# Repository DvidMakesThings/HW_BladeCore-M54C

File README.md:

# BladeCore‑M54C

BladeCore‑M54C is part of the **BladeCore** modular controller series.  
Each BladeCore variant is implemented as a standalone hardware repository, sharing a common architectural philosophy while targeting different microcontrollers and interfaces.

This repository documents the **BladeCore-M54C** hardware, which is based on the **RP2354B** microcontroller and integrates **CAN 2.0B connectivity**.

## BladeCore Series Overview

The BladeCore series consists of the following hardware variants:

| Module | Microcontroller | Primary Interface | Form Factor | Status |
|------|-----------------|-------------------|------------|-------------------|
| [BladeCore‑M40](#)  | RP2040  | —        | -          | Work in progress |
| [BladeCore‑M40E](#) | RP2040  | Ethernet | -          | Work in progress |
| [BladeCore‑M40C](#) | RP2040  | CAN      | -          | Work in progress |
| [BladeCore‑M54](#)  | RP2354B | —        | -          | Work in progress |
| [BladeCore-M54E](https://github.com/DvidMakesThings/HW_BladeCore-M54E) | RP2354B | Ethernet | 2980       | Available |
| [BladeCore-M54C](https://github.com/DvidMakesThings/HW_BladeCore-M54C) | RP2354B | CAN      | 2980       | Available |

### Naming Scheme Explanation

The BladeCore naming scheme encodes the **microcontroller family** and **primary communication interface** directly in the module name:

- **M40** designates an RP2040‑based module  
- **M54** designates an RP2354B‑based module  
- **E** suffix indicates integrated Ethernet support  
- **C** suffix indicates integrated CAN support  

Variants without a suffix represent the **base module** for that microcontroller family, without Ethernet or CAN integrated.

Each BladeCore variant is implemented as a **separate hardware design and repository**.

## Description

BladeCore-M54C is a compact controller module built around the **RP2354B** microcontroller, combined with a **MCP2515T-I/ML CAN controller** and the **TCAN1044AVDRBRQ1** CAN transceiver.  
The module is designed as a **2980-size M.2 M-Key card**, intended to be embedded into a carrier board or system that provides power through the M.2 edge connector.

The design integrates:

*   RP2354B microcontroller
*   External QSPI flash memory
*   External I²C EEPROM
*   Onboard CAN controller and transceiver with 120 Ohm termination
*   Dual‑path USB connectivity with automatic source selection
*   Onboard power regulation and defined power‑up sequencing

This repository contains the schematics and documentation.

- [BladeCore‑M54 schematics (PDF)](src/PDF/BladeCore-M54C_Schematics.pdf).
- [BladeCore‑M54 KiCad folder](src/HardwareDesign/1.0.0/).

### Resources

- **KiCad Libraries:** [src/HardwareDesign/Libraries/KiCad](src/HardwareDesign/Libraries/KiCad)
    - BladeCore‑M54C footprint 
    - BladeCore‑M54C symbol
    - Plain M.2 connector footprint (MDT420E03001)
    - 3D STEP: BladeCore‑M54C + MDT420E03001 assembly
    - 3D STEP: M.2 connector
- **Eagle Libraries:** [src/HardwareDesign/Libraries/Eagle](src/HardwareDesign/Libraries/Eagle)
    - Status: Work in progress

## Hardware Overview

<table>
    <tr>
        <td align="center">
            <br><em>Top view</em>
        </td>
        <td align="center">
            <br><em>Bottom view</em>
        </td>
    </tr>
 </table>

### Form Factor

*   **M.2 2980**
*   **M‑Key**
*   Power and I/O routed through the M.2 edge connector

### Microcontroller

*   **RP2354B**
*   External **12 MHz crystal**
*   Internal 1.1 V core supply generated by the MCU
*   SWD debug interface available
*   GPIOs routed to the M.2 edge connector

### Memory

*   **Integrated Flash**
    *   RP2354B
    *   Capacity: **2 MB**
*   **External QSPI Flash**
    *   W25Q128JVPIQ
    *   Capacity: **16 MB**
*   **External I²C EEPROM**
    *   AT24C256
    *   Capacity: **256 kbit**

***

### CAN

*   **MCP2515T-I/ML CAN controller**
*   **TCAN1044AVDRBRQ1** CAN transceiver
*   Interface to MCU via **SPI**
*   Onboard 120 Ohm termination
*   Dedicated reset and interrupt signals
*   ESD protection

### USB

BladeCore‑M54C supports **two physical USB connection paths**:

1.  **USB routed through the M.2 edge connector** (external host or carrier board USB), and
2.  **Onboard USB‑C connector**.

A **FSUSB42 USB 2.0 high‑speed multiplexer** is used to select which USB path is connected to the RP2354B.

**USB path selection behavior:**

*   By default, the USB data lines are routed to the **M.2 edge connector**.
*   When the **onboard USB‑C connector is plugged in**, the FSUSB42 automatically **redirects the USB data path** from the edge connector to the onboard USB‑C connector.
*   Removing the onboard USB connection restores the default routing to the M.2 edge connector.

This allows the module to be normally operated via a carrier board USB connection, while still enabling direct access through the onboard USB‑C connector when needed, without manual configuration.

***

### Power

*   Input supply: **VBUS / 5 V / 3.3 V** (5V and 3.3V is selectable by onboard solder jumper)
*   **TPS74801** low‑dropout regulator generating 3.3 V in case of 5V power is selected
*   Power‑good signaling with visal feedback (LED)
*   USB VBUS sensing routed to ADC
*   Optional USB‑powered operation depending on component population (as noted in schematics)

### M.2 Connector Pinout

#### Left Side (Odd Pins)

| Pin | Name | F0 | F1 | F2 | F3 | F4 | F5 | F6 | F7 | F8 | F9 |
|----:|------|----|----|----|----|----|----|----|----|----|----| 
| 1 | GND | | | | | | | | | | |
| 3 | GPIO24 | SPI0 TX | UART1 RTS | I2C1 SCL | PWM3 B | SIO | PIO0 | PIO1 | PIO2 | | CLOCK GPOUT1 |
| 5 | GPIO23 | SPI0 TX | UART1 RTS | I2C1 SCL | PWM3 B | SIO | PIO0 | PIO1 | PIO2 | | CLOCK GPOUT1 |
| 7 | GPIO22 | SPI0 SCK | UART1 CTS | I2C1 SDA | PWM3 A | SIO | PIO0 | PIO1 | PIO2 | | CLOCK GPIN1 |
| 9 | GPIO21 | SPI0 CSn | UART1 RX | **I2C0 SCL | PWM2 B | SIO | PIO0 | PIO1 | PIO2 | | CLOCK GPOUT0 |
| 11 | GND | | | | | | | | | | |
| 13 | GPIO20 | SPI0 RX | UART1 TX | **I2C0 SDA | PWM2 A | SIO | PIO0 | PIO1 | PIO2 | | CLOCK GPIN0 |
| 15 | GPIO19 | SPI0 TX | UART0 RTS | I2C1 SCL | PWM1 B | SIO | PIO0 | PIO1 | PIO2 | | QMI CS1n |
| 17 | GPIO18 | SPI0 SCK | UART0 CTS | I2C1 SDA | PWM1 A | SIO | PIO0 | PIO1 | PIO2 | | |
| 19 | GPIO17 | SPI0 CSn | UART0 RX | **I2C0 SCL | PWM0 B | SIO | PIO0 | PIO1 | PIO2 | | |
| 21 | GPIO16 | SPI0 RX | UART0 TX | **I2C0 SDA | PWM0 A | SIO | PIO0 | PIO1 | PIO2 | | |
| 23 | GND | | | | | | | | | | |
| 25 | GPIO15 | *SPI1 TX | UART0 RTS | I2C1 SCL | PWM7 B | SIO | PIO0 | PIO1 | PIO2 | | CLOCK GPOUT1 |
| 27 | GPIO14 | *SPI1 SCK | UART0 CTS | I2C1 SDA | PWM7 A | SIO | PIO0 | PIO1 | PIO2 | | CLOCK GPIN1 |
| 29 | GPIO13 | *SPI1 CSn | UART0 RX | **I2C0 SCL | PWM6 B | SIO | PIO0 | PIO1 | PIO2 | | CLOCK GPOUT0 |
| 31 | GPIO12 | *SPI1 RX | UART0 TX | **I2C0 SDA | PWM6 A | SIO | PIO0 | PIO1 | PIO2 | | CLOCK GPIN0 |
| 33 | GPIO11 | *SPI1 TX | UART1 RTS | I2C1 SCL | PWM5 B | SIO | PIO0 | PIO1 | PIO2 | | |
| 35 | GPIO10 | *SPI1 SCK | UART1 CTS | I2C1 SDA | PWM5 A | SIO | PIO0 | PIO1 | PIO2 | | |
| 37 | GPIO9 | *SPI1 CSn | UART1 RX | **I2C0 SCL | PWM4 B | SIO | PIO0 | PIO1 | PIO2 | | |
| 39 | GPIO8 | *SPI1 RX | UART1 TX | **I2C0 SDA | PWM4 A | SIO | PIO0 | PIO1 | PIO2 | | QMI CS1n |
| 41 | GND | | | | | | | | | | |
| 43 | GPIO7 | SPI0 TX | UART1 RTS | I2C1 SCL | PWM3 B | SIO | PIO0 | PIO1 | PIO2 | | |
| 45 | GPIO6 | SPI0 SCK | UART1 CTS | I2C1 SDA | PWM3 A | SIO | PIO0 | PIO1 | PIO2 | | |
| 47 | GPIO5 | SPI0 CSn | UART1 RX | **I2C0 SCL | PWM2 B | SIO | PIO0 | PIO1 | PIO2 | | |
| 49 | GPIO4 | SPI0 RX | UART1 TX | **I2C0 SDA | PWM2 A | SIO | PIO0 | PIO1 | PIO2 | | |
| 51 | GPIO3 | SPI0 TX | UART0 RTS | I2C1 SCL | PWM1 B | SIO | PIO0 | PIO1 | PIO2 | | |
| 53 | GPIO2 | SPI0 SCK | UART0 CTS | I2C1 SDA | PWM1 A | SIO | PIO0 | PIO1 | PIO2 | | |
| 55 | GPIO1 | SPI0 CSn | UART0 RX | **I2C0 SCL | PWM0 B | SIO | PIO0 | PIO1 | PIO2 | | TRACECLK |
| 57 | GPIO0 | SPI0 RX | UART0 TX | **I2C0 SDA | PWM0 A | SIO | PIO0 | PIO1 | PIO2 | | QMI CS1n |
| 67 | GND | | | | | | | | | | |
| 69 | USB_D+ | | | | | | | | | | |
| 71 | USB_D- | | | | | | | | | | |
| 73 | GND | | | | | | | | | | |
| 75 | VBUS | | | | | | | | | | |

#### Right Side (Even Pins)

| Pin | Name | F0 | F1 | F2 | F3 | F4 | F5 | F6 | F7 | F8 | F9 |
|----:|------|----|----|----|----|----|----|----|----|----|----| 
| 2 | GND | | | | | | | | | | |
| 4 | GPIO27 | *SPI1 TX | UART1 RTS | I2C1 SCL | PWM5 B | SIO | PIO0 | PIO1 | PIO2 | | |
| 6 | GPIO26 | *SPI1 SCK | UART1 CTS | I2C1 SDA | PWM5 A | SIO | PIO0 | PIO1 | PIO2 | | |
| 8 | GPIO25 | *SPI1 CSn | UART1 RX | **I2C0 SCL | PWM4 B | SIO | PIO0 | PIO1 | PIO2 | | CLOCK GPOUT3 |
| 10 | 3V3_OUT | | | | | | | | | | |
| 12 | 3V3_OUT | | | | | | | | | | |
| 14 | +5V_IN | | | | | | | | | | |
| 16 | +5V_IN | | | | | | | | | | |
| 18 | GND | | | | | | | | | | |
| 20 | GND | | | | | | | | | | |
| 22 | GND | | | | | | | | | | |
| 24 | GND | | | | | | | | | | |
| 26 | GND | | | | | | | | | | |
| 28 | CAN_P | | | | | | | | | | |
| 30 | CAN_N | | | | | | | | | | |
| 32 | GND | | | | | | | | | | |
| 34 | GPIO37 |  | SPI0 CSn | UART1 RX | **I2C0 SCL | PWM10 B | SIO | PIO0 | PIO1 | PIO2 |  |
| 36 | GPIO38 |  | SPI0 SCK | UART1 CTS | I2C1 SDA | PWM11 A | SIO | PIO0 | PIO1 | PIO2 |  |
| 38 | GND | | | | | | | | | | |
| 40 | GPIO39 |  | SPI0 TX | UART1 RTS | I2C1 SCL | PWM11 B | SIO | PIO0 | PIO1 | PIO2 |  |
| 42 | GND | | | | | | | | | | |
| 44 | GND | | | | | | | | | | |
| 46 | ADC0/GPIO40 |  | *SPI1 RX | UART1 TX | **I2C0 SDA | PWM8 A | SIO | PIO0 | PIO1 | PIO2 |  |
| 48 | ADC1/GPIO41 |  | *SPI1 CSn | UART1 RX | **I2C0 SCL | PWM8 B | SIO | PIO0 | PIO1 | PIO2 |  |
| 50 | ADC2/GPIO42 |  | *SPI1 SCK | UART1 CTS | I2C1 SDA | PWM9 A | SIO | PIO0 | PIO1 | PIO2 |  |
| 52 | ADC3/GPIO43 |  | *SPI1 TX | UART1 RTS | I2C1 SCL | PWM9 B | SIO | PIO0 | PIO1 | PIO2 |  |
| 54 | ADC4/GPIO44 |  | *SPI1 RX | UART0 TX | **I2C0 SDA | PWM10 A | SIO | PIO0 | PIO1 | PIO2 |  |
| 56 | ADC5/GPIO45 |  | *SPI1 CSn | UART0 RX | **I2C0 SCL | PWM10 B | SIO | PIO0 | PIO1 | PIO2 |  |
| 58 | GND | | | | | | | | | | |
| 68 | GND | | | | | | | | | | |
| 70 | GND | | | | | | | | | | |
| 72 | VBUS | | | | | | | | | | |
| 74 | VBUS | | | | | | | | | | |
| SH1 | SHIELD | | | | | | | | | | |

*SPI1 is used for the onboard CAN controller (MCP2515T)

**I2C0 is used for the onboard EEPROM (AT24C256)

## Revision History

| Revision | Date       | Notes            |
| -------- | ---------- | ---------------- |
| 1.0.0    | 2026‑01‑31 | Initial creation |

## Notes

*   This documentation intentionally avoids assumptions about firmware features, supported protocols, or software behavior.
*   All statements are derived from the provided schematics and explicit design notes.
*   Component‑level limits and behavior should be verified against the respective datasheets.

## License
### Hardware Components
Hardware designs, schematics, and related documentation are licensed under the **Creative Commons Attribution-NonCommercial-ShareAlike 4.0 International License (CC BY-NC-SA 4.0)**. See the [Hardware License](LICENSE-CC-BY-NC-SA) file for details.

#### What CC BY-NC-SA 4.0 means:

- ✅ **You can** study, modify, and distribute the hardware designs
- ✅ **You can** create derivative works for personal, educational, or non-commercial use
- ✅ **You can** build this project for your own personal use

- ⚠️ **You must** give appropriate credit and indicate if changes were made
- ⚠️ **You must** share any modifications under the same license terms
- ⚠️ **You must** include the original license and copyright notices

- ❌ **You cannot** use the designs for commercial purposes without explicit permission
- ❌ **You cannot** manufacture and sell products based on these designs without a commercial license
- ❌ **You cannot** create closed-source derivatives for commercial purposes
- ❌ **You cannot** use the designer's trademarks without permission

### Commercial & Enterprise Use

Commercial use of this project is prohibited without obtaining a separate commercial license. If you are interested in:

- Manufacturing and selling products based on these designs
- Incorporating these designs into commercial products
- Any other commercial applications

Please contact me through any of the channels listed in the [Contact](#contact) section to discuss commercial licensing arrangements. Commercial licenses are available with reasonable terms to support ongoing development.

## Contact

For questions or feedback:
- **Email:** [info@dmt-hw.com](mailto:info@dmt-hw.com)
- **GitHub:** [DvidMakesThings](https://github.com/DvidMakesThings)

## Contributing

Contributions are welcome! As this is an early-stage project, please reach out before 
making substantial changes:

1. Fork the repository
2. Create a feature branch (`git checkout -b feature/concept`)
3. Commit your changes (`git commit -m 'Add concept'`)
4. Push to the branch (`git push origin feature/concept`)
5. Open a Pull Request with a detailed description

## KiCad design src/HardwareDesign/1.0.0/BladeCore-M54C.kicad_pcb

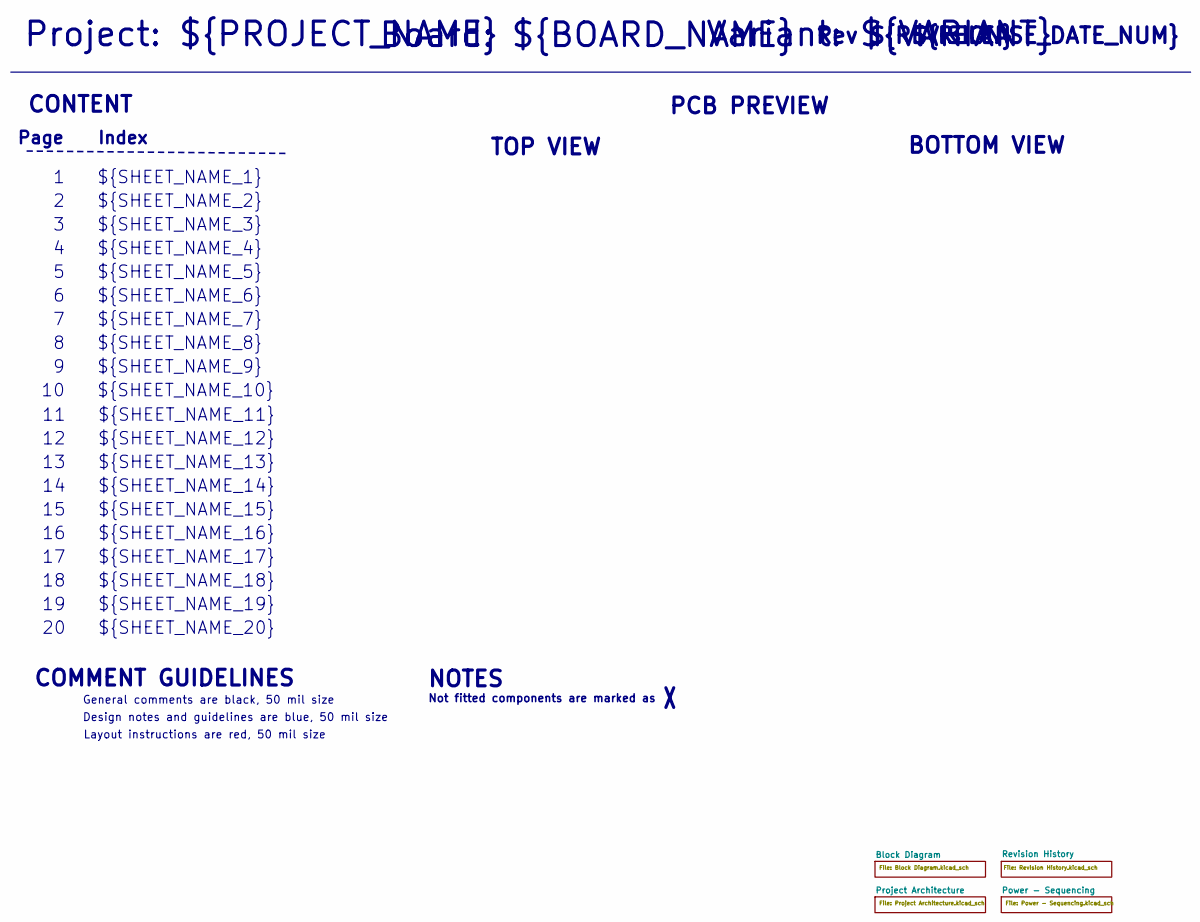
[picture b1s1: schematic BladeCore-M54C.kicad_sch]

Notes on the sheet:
${SHEET_NAME_12}
${SHEET_NAME_8}
${SHEET_NAME_2}
${SHEET_NAME_5}
${SHEET_NAME_20}
Page
PCB PREVIEW
${RELEASE_DATE_NUM}
CONTENT
${SHEET_NAME_11}
${SHEET_NAME_6}
Rev ${REVISION}
${SHEET_NAME_15}
BOTTOM VIEW
${SHEET_NAME_14}
${SHEET_NAME_17}
${SHEET_NAME_18}
${SHEET_NAME_7}
Not fitted components are marked as
Project: ${PROJECT_NAME}
NOTES
Design notes and guidelines are blue, 50 mil size
${SHEET_NAME_1}
${SHEET_NAME_9}
Board: ${BOARD_NAME}
General comments are black, 50 mil size
${SHEET_NAME_16}
${SHEET_NAME_3}
Variant: ${VARIANT}
${SHEET_NAME_19}
TOP VIEW
${SHEET_NAME_10}
Index
${SHEET_NAME_13}
${SHEET_NAME_4}
COMMENT GUIDELINES
Layout instructions are red, 50 mil size

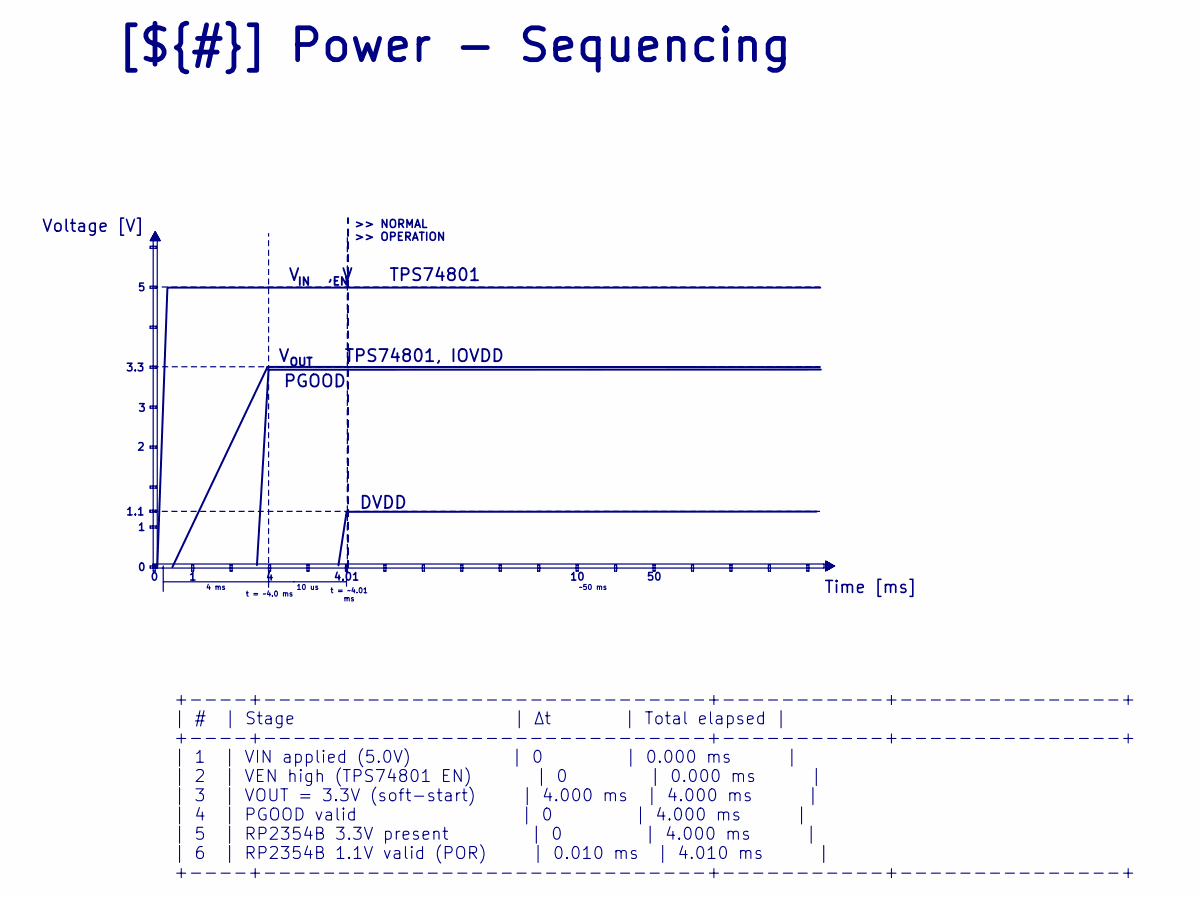
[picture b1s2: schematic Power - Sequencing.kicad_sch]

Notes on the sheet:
Voltage [V]
+----+------------------------------+-----------+---------------+ | # | Stage | Δt | Total elapsed | +----+------------------------------+-----------+---------------+ | 1 | VIN applied (5.0V) | 0 | 0.000 ms | | 2 | VEN high (TPS74801 EN) | 0 | 0.000 ms | | 3 | VOUT = 3.3V (soft-start) | 4.000 ms | 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
>> NORMAL >> OPERATION
Time [ms]
10 us
4.01
DVDD
t = ~4.01 ms
3.3
~50 ms
V , V TPS74801
t = ~4.0 ms
PGOOD
1.1
4 ms
OUT
V TPS74801, IOVDD
[${#}] ${TITLE}

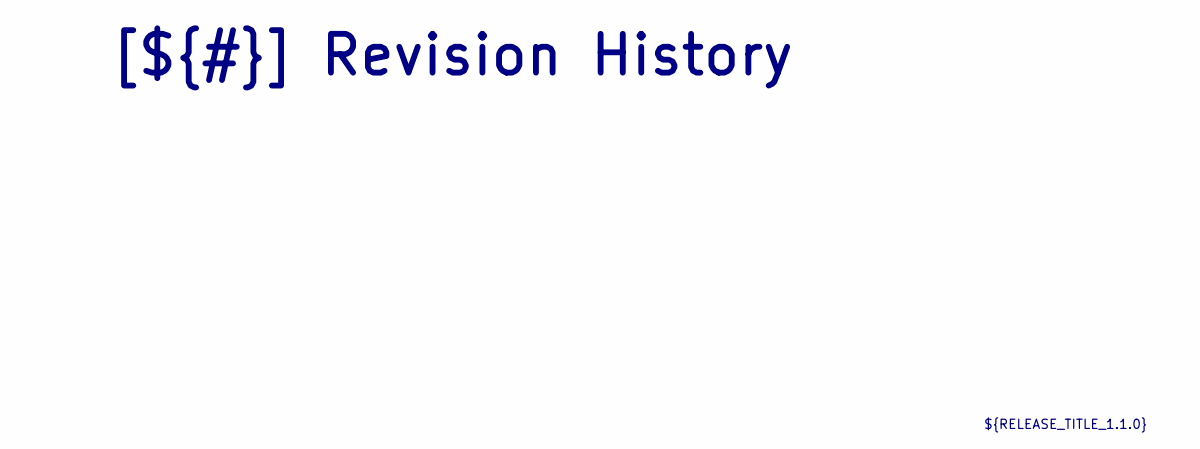
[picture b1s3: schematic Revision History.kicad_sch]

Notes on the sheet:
[${#}] ${TITLE}
${RELEASE_TITLE_1.1.0}

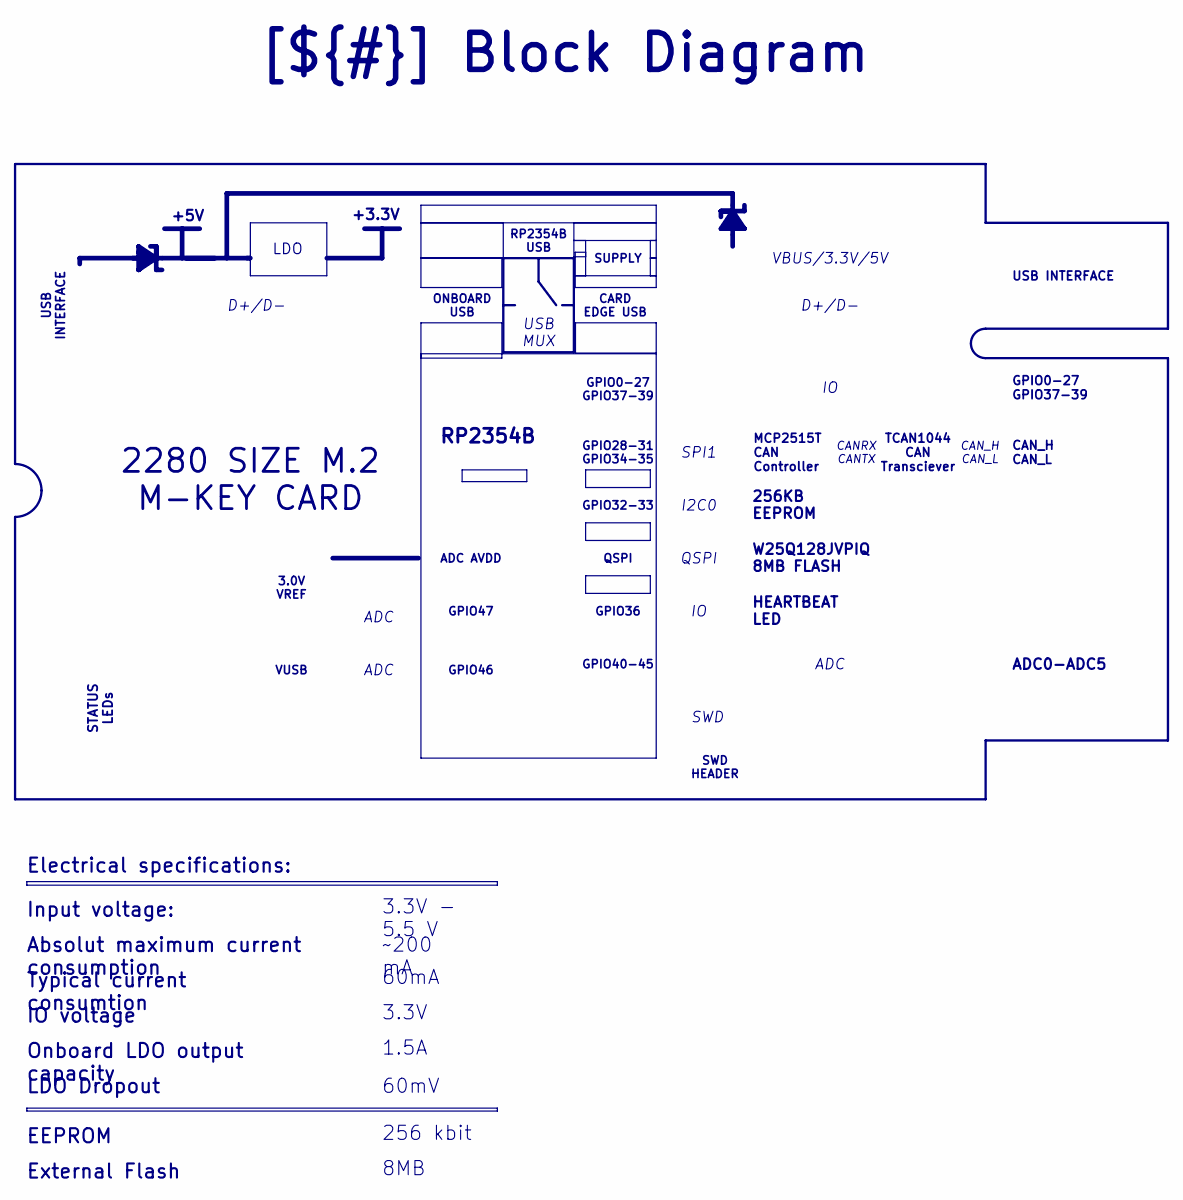
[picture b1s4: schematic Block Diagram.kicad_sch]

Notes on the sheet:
+3.3V
RP2354B
2280 SIZE M.2 M-KEY CARD
+5V
USB INTERFACE
LDO Dropout
IO voltage
256KB EEPROM
VBUS/3.3V/5V
1.5A
CARD EDGE USB
W25Q128JVPIQ 8MB FLASH
3.3V - 5.5 V
ADC0-ADC5
SWD HEADER
LDO
3.3V
GPIO0-27 GPIO37-39
CAN_H CAN_L
SPI1
MCP2515T CAN Controller
TCAN1044 CAN Transciever
GPIO40-45
ADC
QSPI
3.0V VREF
RP2354B USB
GPIO32-33
[${#}] ${TITLE}
~200 mA
Input voltage:
STATUS LEDs
EEPROM
GPIO46
256 kbit
Electrical specifications:
SWD
GPIO47
GPIO36
GPIO28-31 GPIO34-35

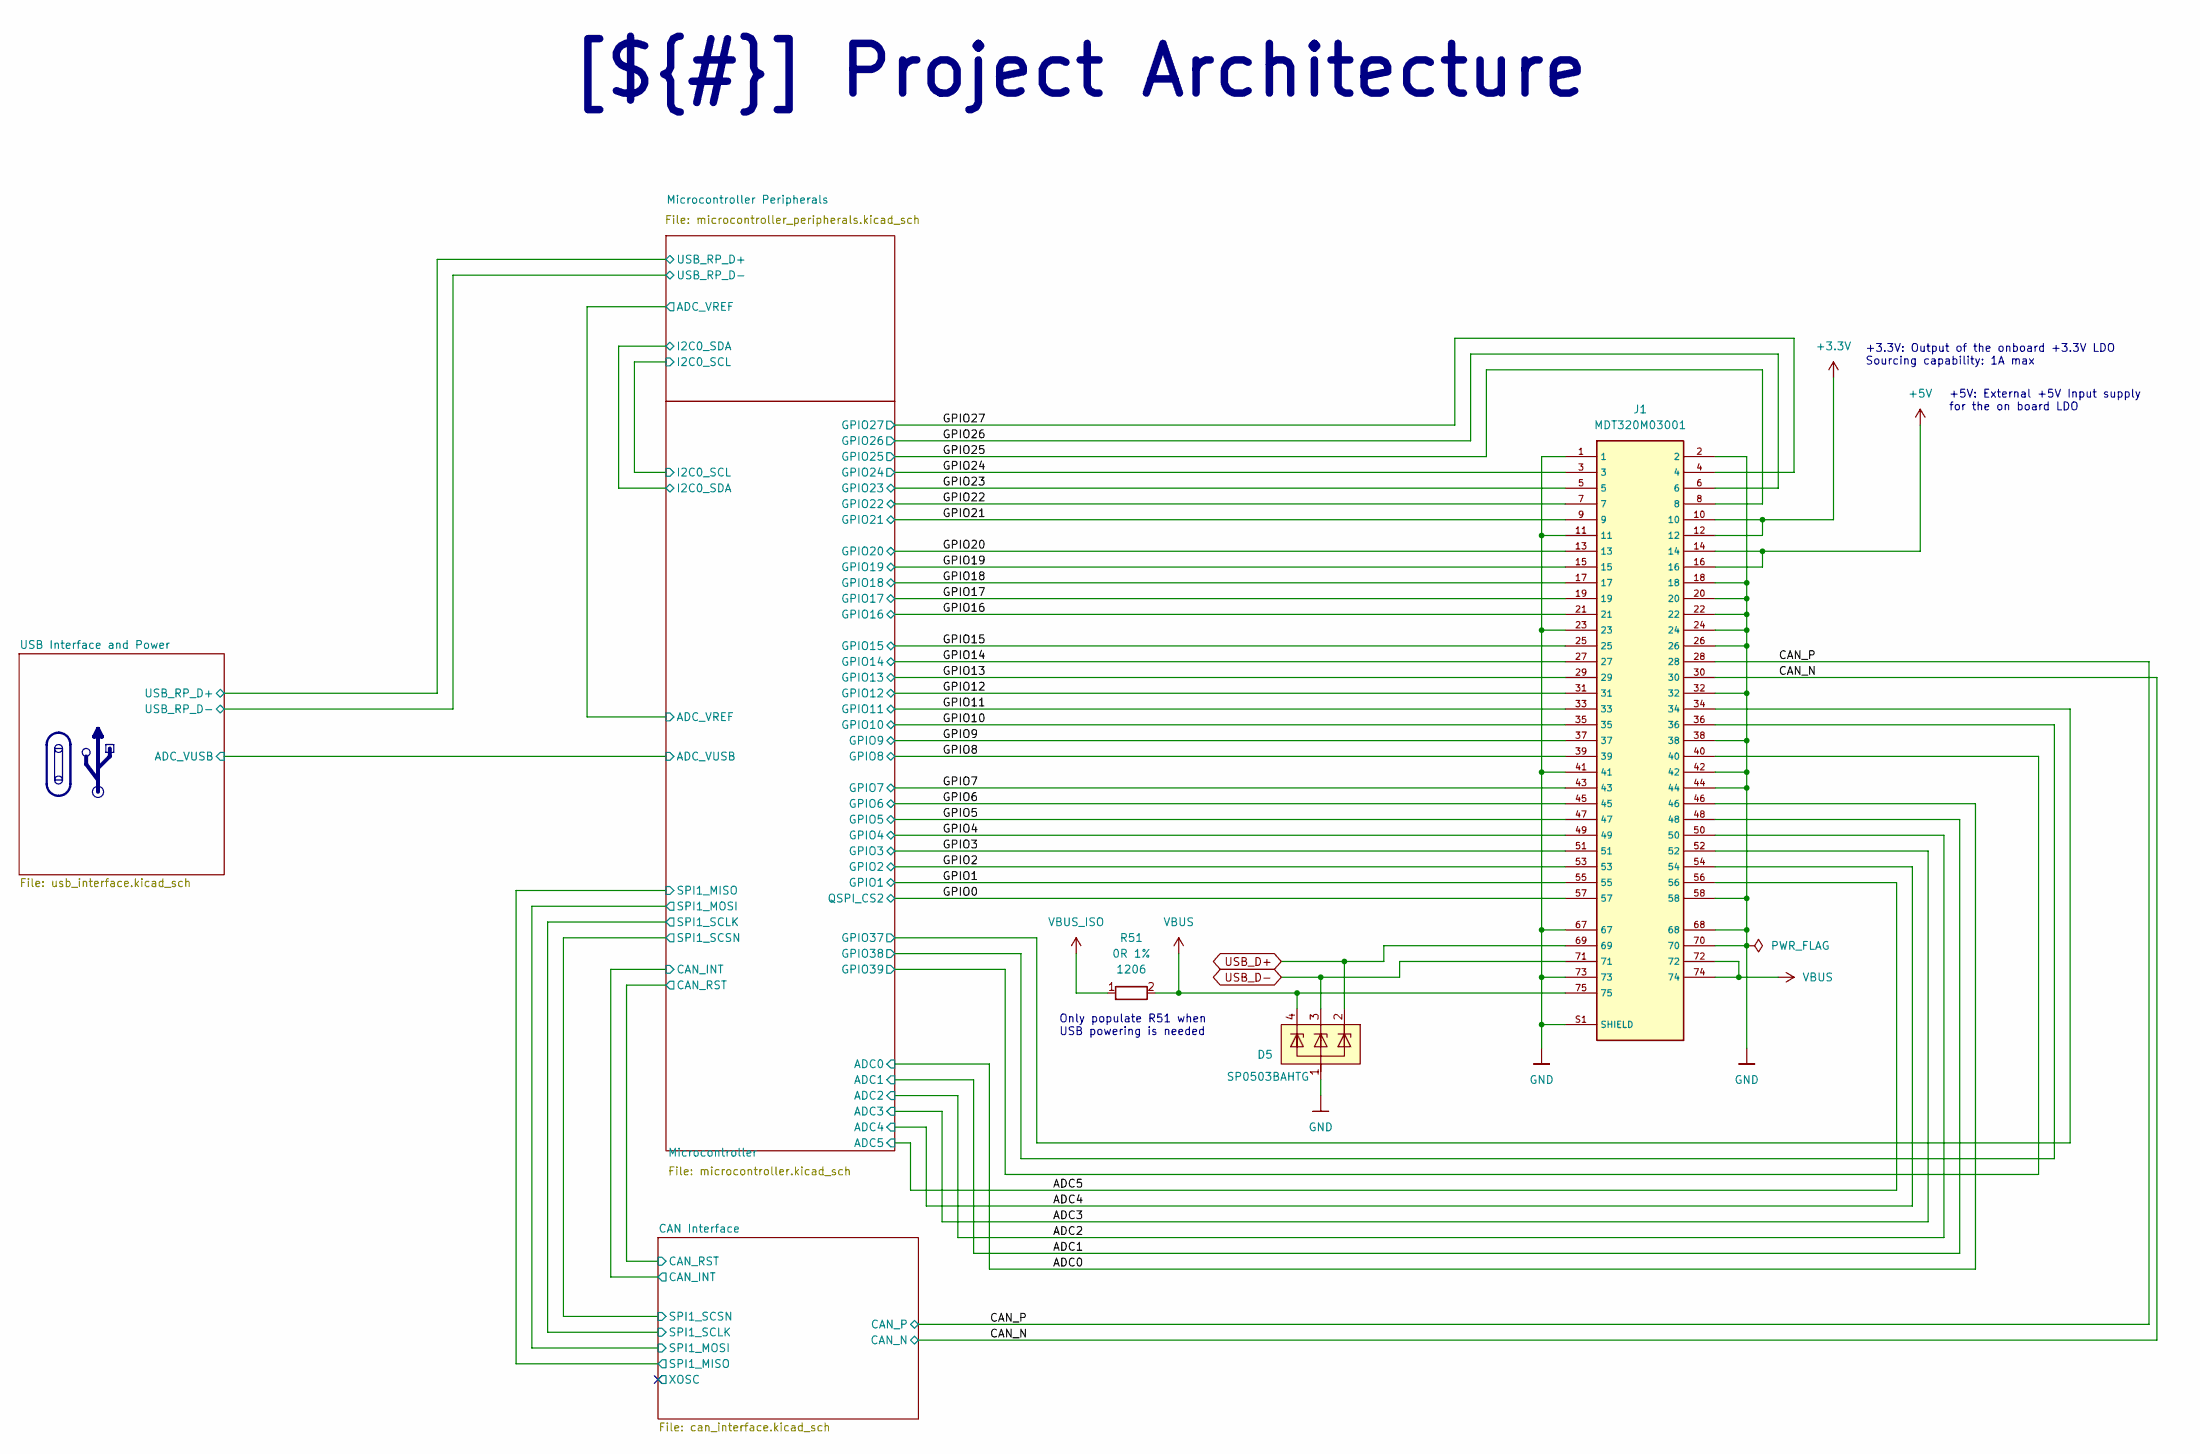
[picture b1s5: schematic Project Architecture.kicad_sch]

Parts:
D5: SP0503BAHTG; SOT143; MPN SP0503BAHTG; LCSC_PART C3040626
J1: MDT320M03001; M.2-M-KEY_Card_Plain
R51: 0R 1%; R_1206_3216Metric; LCSC_PART C205296

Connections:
+3.3V: J1.10, J1.12; also elsewhere on the board
+5V: J1.14, J1.16; also elsewhere on the board
/Project Architecture/ADC0: J1.46; also elsewhere on the board
/Project Architecture/ADC1: J1.48; also elsewhere on the board
/Project Architecture/ADC2: J1.50; also elsewhere on the board
/Project Architecture/ADC3: J1.52; also elsewhere on the board
/Project Architecture/ADC4: J1.54; also elsewhere on the board
/Project Architecture/ADC5: J1.56; also elsewhere on the board
/Project Architecture/CAN_N: J1.30; also elsewhere on the board
/Project Architecture/CAN_P: J1.28; also elsewhere on the board
/Project Architecture/GPIO0: J1.57; also elsewhere on the board
/Project Architecture/GPIO1: J1.55; also elsewhere on the board
/Project Architecture/GPIO2: J1.53; also elsewhere on the board
/Project Architecture/GPIO3: J1.51; also elsewhere on the board
/Project Architecture/GPIO4: J1.49; also elsewhere on the board
/Project Architecture/GPIO5: J1.47; also elsewhere on the board
/Project Architecture/GPIO6: J1.45; also elsewhere on the board
/Project Architecture/GPIO7: J1.43; also elsewhere on the board
/Project Architecture/GPIO8: J1.39; also elsewhere on the board
/Project Architecture/GPIO9: J1.37; also elsewhere on the board
/Project Architecture/GPIO10: J1.35; also elsewhere on the board
/Project Architecture/GPIO11: J1.33; also elsewhere on the board
/Project Architecture/GPIO12: J1.31; also elsewhere on the board
/Project Architecture/GPIO13: J1.29; also elsewhere on the board
/Project Architecture/GPIO14: J1.27; also elsewhere on the board
/Project Architecture/GPIO15: J1.25; also elsewhere on the board
/Project Architecture/GPIO16: J1.21; also elsewhere on the board
/Project Architecture/GPIO17: J1.19; also elsewhere on the board
/Project Architecture/GPIO18: J1.17; also elsewhere on the board
/Project Architecture/GPIO19: J1.15; also elsewhere on the board
/Project Architecture/GPIO20: J1.13; also elsewhere on the board
/Project Architecture/GPIO21: J1.9; also elsewhere on the board
/Project Architecture/GPIO22: J1.7; also elsewhere on the board
/Project Architecture/GPIO23: J1.5; also elsewhere on the board
/Project Architecture/GPIO24: J1.3; also elsewhere on the board
/Project Architecture/GPIO25: J1.8; also elsewhere on the board
/Project Architecture/GPIO26: J1.6; also elsewhere on the board
/Project Architecture/GPIO27: J1.4; also elsewhere on the board
/Project Architecture/Microcontroller/GPIO37: J1.34; also elsewhere on the board
/Project Architecture/Microcontroller/GPIO38: J1.36; also elsewhere on the board
/Project Architecture/Microcontroller/GPIO39: J1.40; also elsewhere on the board
GND: D5.1, J1.1, J1.2, J1.11, J1.18, J1.20, J1.22, J1.23, J1.24, J1.26, J1.32, J1.38, J1.41, J1.42, J1.44, J1.58, J1.67, J1.68, J1.70, J1.73, J1.S1 (SHIELD); also elsewhere on the board
USB_D+: D5.2, J1.69; also elsewhere on the board
USB_D-: D5.3, J1.71; also elsewhere on the board
VBUS: D5.4, J1.72, J1.74, J1.75, R51.2; also elsewhere on the board
VBUS_ISO: R51.1; also elsewhere on the board

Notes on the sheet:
Only populate R51 when USB powering is needed
+3.3V: Output of the onboard +3.3V LDO Sourcing capability: 1A max
+5V: External +5V Input supply for the on board LDO
[${#}] ${TITLE}

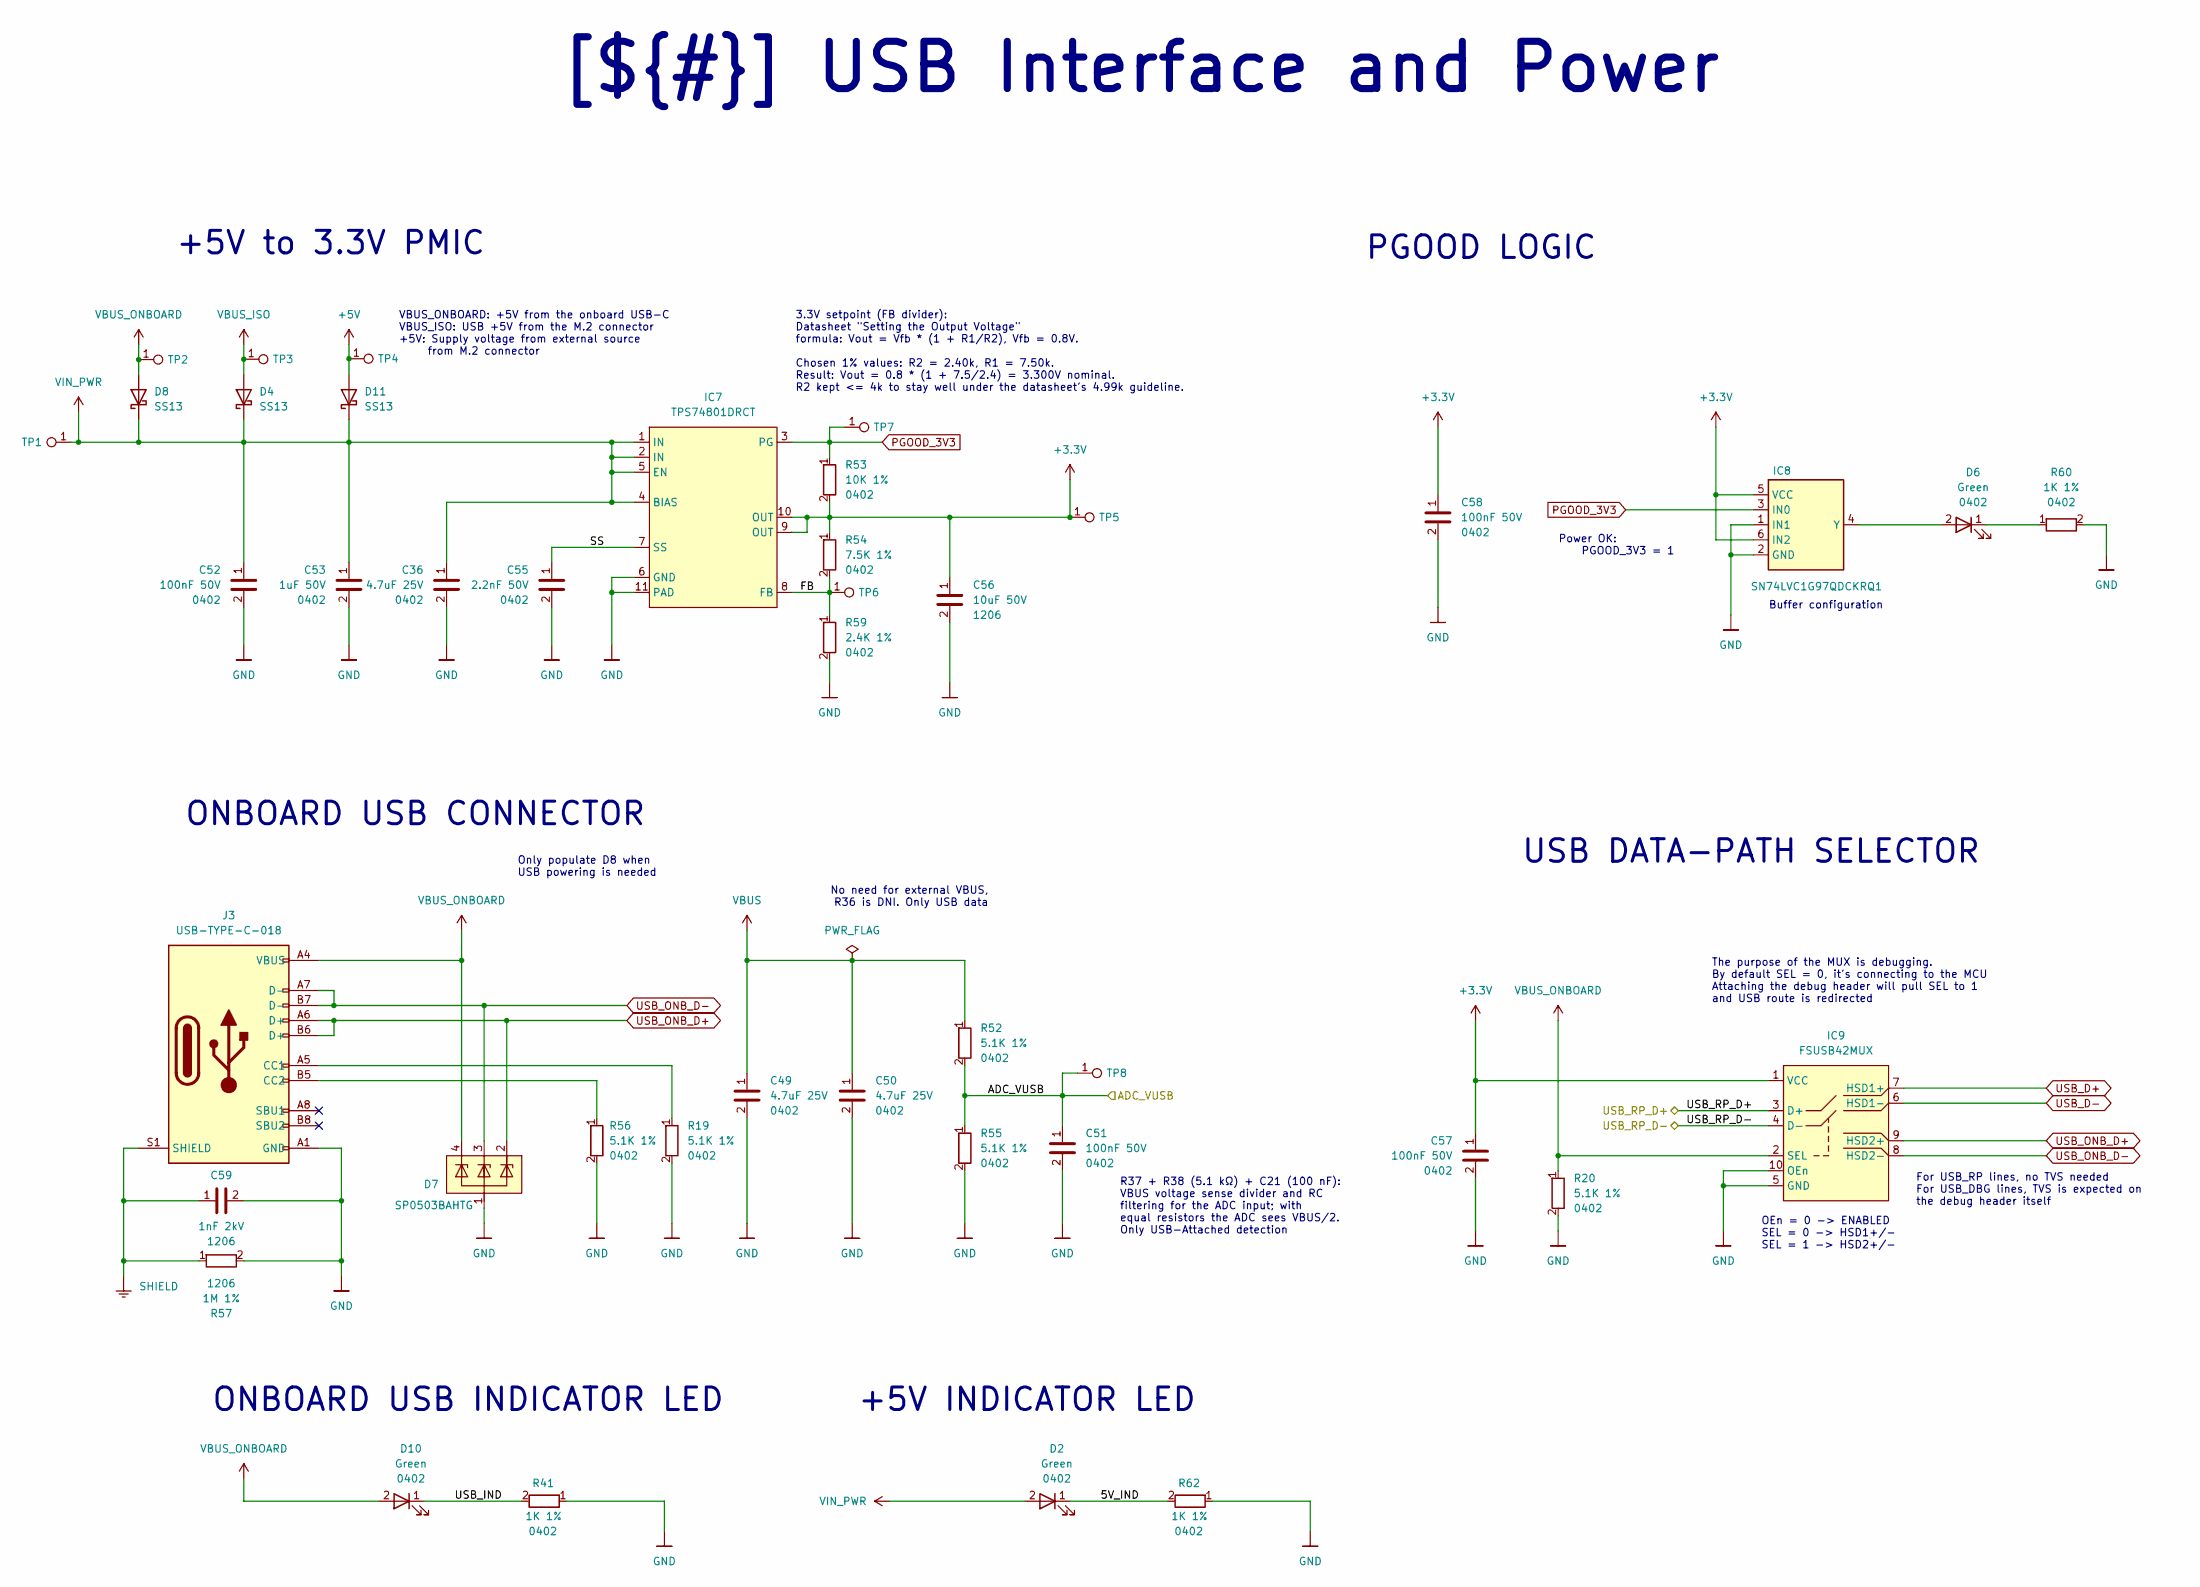
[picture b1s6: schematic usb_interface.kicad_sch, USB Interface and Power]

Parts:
C36, C49, C50: 4.7uF 25V; C_0402_1005Metric; LCSC_PART C22367824
C51, C52, C57, C58: 100nF 50V; C_0402_1005Metric; LCSC_PART C307331
C53: 1uF 50V; C_0402_1005Metric; LCSC_PART C1518208
C55: 2.2nF 50V; C_0402_1005Metric; MPN CC0402KRX7R9BB222; LCSC_PART C106861
C56: 10uF 50V; C_1206_3216Metric; MPN CL31A106KBHNNNE; LCSC_PART C13585
C59: 1nF 2kV; C_1206_3216Metric; LCSC_PART C173242
D2, D6, D10: Green; LED_0402_1005Metric; MPN XL-1005UGC; LCSC_PART C965793
D4, D8, D11: SS13; D_SMA
D7: SP0503BAHTG; SOT143; MPN SP0503BAHTG; LCSC_PART C3040626
IC7: TPS74801DRCT; VSON-10-1EP_3x3mm_P0.5mm_EP1.65x2.4mm_ThermalVias; MPN TPS74801DRCT; LCSC_PART C882845
IC8: SN74LVC1G97QDCKRQ1; SOT-363_SC-70-6; MPN SN74LVC1G97QDCKRQ1; LCSC_PART C179911
IC9: FSUSB42MUX; MSOP-10_3x3mm_P0.5mm; MPN FSUSB42MUX; LCSC_PART C11355
J3: USB-TYPE-C-018; USB_C_Receptacle_HCTL_HC-TYPE-C-16P-01A; MPN USB-TYPE-C-018; LCSC_PART C2927038
R19, R20, R52, R55, R56: 5.1K 1%; R_0402_1005Metric; LCSC_PART C25905
R41, R60, R62: 1K 1%; R_0402_1005Metric; LCSC_PART C11702
R53: 10K 1%; R_0402_1005Metric; LCSC_PART C25744
R54: 7.5K 1%; R_0402_1005Metric; LCSC_PART C25918
R57: 1M 1%; R_1206_3216Metric; LCSC_PART C17927
R59: 2.4K 1%; R_0402_1005Metric; LCSC_PART C25882
TP1, TP2, TP3, TP4, TP5, TP6, TP7, TP8: TestPoint_0.6mm

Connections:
+3.3V: C56.1, C57.1, C58.1, IC7.9 (OUT), IC7.10 (OUT), IC8.5 (VCC), IC8.6 (IN2), IC9.1 (VCC), R53.2, R54.1, TP5.1; also elsewhere on the board
+5V: D11.2 (A), TP4.1; also elsewhere on the board
/Project Architecture/Microcontroller/ADC_VUSB: C51.1, R52.2, R55.1, TP8.1; also elsewhere on the board
/Project Architecture/USB Interface and Power/5V_IND: D2.1, R62.2
/Project Architecture/USB Interface and Power/FB: IC7.8 (FB), R54.2, R59.1, TP6.1
/Project Architecture/USB Interface and Power/SS: C55.1, IC7.7 (SS)
/Project Architecture/USB Interface and Power/USB_IND: D10.1, R41.2
/Project Architecture/USB Interface and Power/USB_RP_D+: IC9.3 (D+); also elsewhere on the board
/Project Architecture/USB Interface and Power/USB_RP_D-: IC9.4 (D-); also elsewhere on the board
GND: C36.2, C49.2, C50.2, C51.2, C52.2, C53.2, C55.2, C56.2, C57.2, C58.2, C59.2, D7.1, IC7.6 (GND), IC7.11 (PAD), IC8.1 (IN1), IC8.2 (GND), IC9.5 (GND), IC9.10 (OEn), J3.A1 (GND), J3.A12 (GND), J3.B1 (GND), J3.B12 (GND), R19.2, R20.2, R41.1, R55.2, R56.2, R57.2, R59.2, R60.2, R62.1; also elsewhere on the board
unnamed: D6.1, R60.1
unnamed: D6.2, IC8.4 (Y)
unnamed: J3.A5 (CC1), R19.1
unnamed: J3.B5 (CC2), R56.1
PGOOD_3V3: IC7.3 (PG), IC8.3 (IN0), R53.1, TP7.1
SHIELD: C59.1, J3.S1 (SHIELD), R57.1
USB_D+: IC9.7 (HSD1+); also elsewhere on the board
USB_D-: IC9.6 (HSD1-); also elsewhere on the board
USB_ONB_D+: D7.2, IC9.9 (HSD2+), J3.A6 (D+), J3.B6 (D+)
USB_ONB_D-: D7.3, IC9.8 (HSD2-), J3.A7 (D-), J3.B7 (D-)
VBUS: C49.1, C50.1, R52.1; also elsewhere on the board
VBUS_ISO: D4.2 (A), TP3.1; also elsewhere on the board
VBUS_ONBOARD: D7.4, D8.2 (A), D10.2, IC9.2 (SEL), J3.A4 (VBUS), J3.A9 (VBUS), J3.B4 (VBUS), J3.B9 (VBUS), R20.1, TP2.1
VIN_PWR: C36.1, C52.1, C53.1, D2.2, D4.1 (K), D8.1 (K), D11.1 (K), IC7.1 (IN), IC7.2 (IN), IC7.4 (BIAS), IC7.5 (EN), TP1.1; also elsewhere on the board

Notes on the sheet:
OEn = 0 -> ENABLED SEL = 0 -> HSD1+/- SEL = 1 -> HSD2+/-
ONBOARD USB INDICATOR LED
USB DATA-PATH SELECTOR
VBUS_ONBOARD: +5V from the onboard USB-C VBUS_ISO: USB +5V from the M.2 connector +5V: Supply voltage from external source from M.2 connector
No need for external VBUS, R36 is DNI. Only USB data
+5V to 3.3V PMIC
3.3V setpoint (FB divider): Datasheet "Setting the Output Voltage" formula: Vout = Vfb * (1 + R1/R2), Vfb = 0.8V. Chosen 1% values: R2 = 2.40k, R1 = 7.50k. Result: Vout = 0.8 * (1 + 7.5/2.4) = 3.300V nominal. R2 kept <= 4k to stay well under the datasheet's 4.99k guideline.
ONBOARD USB CONNECTOR
For USB_RP lines, no TVS needed For USB_DBG lines, TVS is expected on the debug header itself
R37 + R38 (5.1 kΩ) + C21 (100 nF): VBUS voltage sense divider and RC filtering for the ADC input; with equal resistors the ADC sees VBUS/2. Only USB-Attached detection
+5V INDICATOR LED
Power OK: PGOOD_3V3 = 1
Buffer configuration
PGOOD LOGIC
Only populate D8 when USB powering is needed
The purpose of the MUX is debugging. By default SEL = 0, it's connecting to the MCU Attaching the debug header will pull SEL to 1 and USB route is redirected
[${#}] ${TITLE}
